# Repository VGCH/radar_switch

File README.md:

# IoT Модуль управления освещением с радарным датчиком

Работает как самостоятельное утройство, так и в составе умного дома Home Assistant:

В модуле реализованы следующие сервисы

> mDNS

> SSDP/UPnP

> Captive Portal

> MQTT Discovery

## Конфигурация устройства в Home Assistant:

## Веб-интерфейс:

Репозиторий содержит исходники:

> Прошивки устройства

> Печатной платы

> Модели корпуса

## В веб-интерфейсе добавлен график для отображения дистанции в реальном времени:

Полное описание в статье на Хабр

[Ссылка на статью ](https://habr.com/ru/articles/979262/)

[Поддержать донатом ](https://dalink.to/cyberex_tech)

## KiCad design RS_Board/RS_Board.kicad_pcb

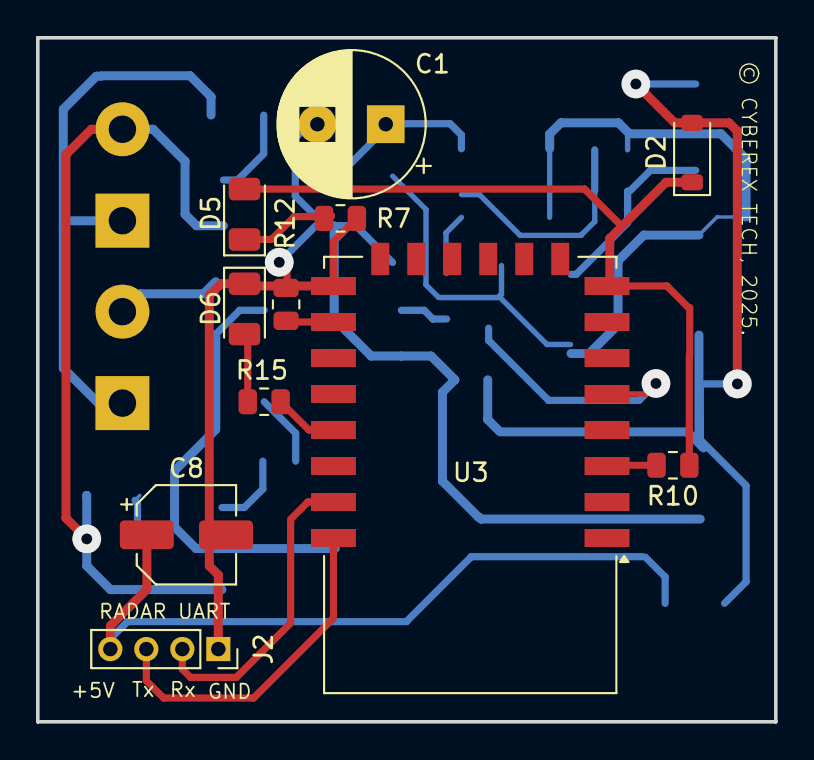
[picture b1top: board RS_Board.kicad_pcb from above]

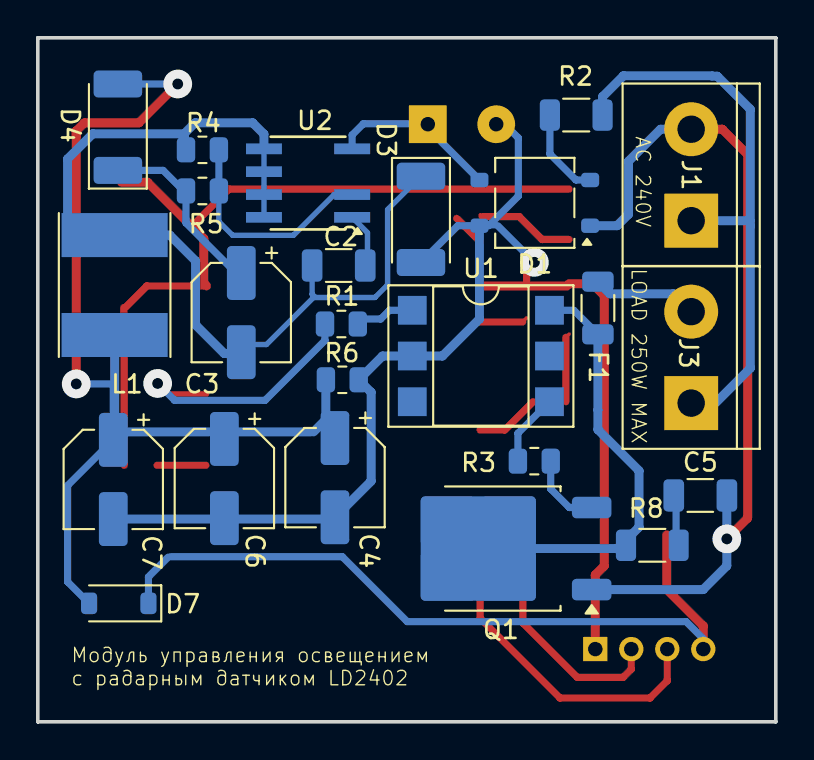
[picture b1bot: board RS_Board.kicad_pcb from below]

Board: 2 copper layers, 41.0 x 38.0 mm, 35 parts (24 on the bottom side), 26 nets.

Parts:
C1: 4.3uF 400V; CP_Radial_D8.0mm_P3.80mm
C2: 100n; C_1206_3216Metric
C3: 45uF 135V; CP_Elec_5x5.4
C4, C6, C7: 220uF 10V; CP_Elec_5x5.4
C5: 10n; C_1206_3216Metric
C8: 220uF 6.3V; CP_Elec_5x5.4
D1: RMB4S; TO-269AA
D2, D7: RB051L-40TE25; D_SOD-123
D3, D4: UF4005 US1J; D_MELF
D5, D6: LED; LED_1206_3216Metric
F1: 1А; R_1206_3216Metric
J1: 240V AC; TerminalBlock_bornier-2_P5.08mm
J2: LD 2402; PinSocket_1x04_P2.00mm_Vertical
J3: LOAD 250W MAX; TerminalBlock_bornier-2_P5.08mm
L1: 1mH; L_Taiyo-Yuden_NR-60xx_HandSoldering
Q1: BT136-600; TO-252-2
R1: 330; R_0805_2012Metric
R2: 0.5; R_1206_3216Metric
R3: 600; R_0805_2012Metric
R4: 1.7k; R_0805_2012Metric
R5: 2.7k; R_0805_2012Metric
R6: 1.5k; R_0805_2012Metric
R7, R10, R12: 1k; R_0805_2012Metric
R8: 39; R_1206_3216Metric
R15: 470; R_0805_2012Metric
U1: MOC3052M; DIP-6_W7.62mm_SMDSocket_SmallPads
U2: LNK362D; PowerIntegrations_SO-8C
U3: ESP-12F; ESP-12E

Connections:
unnamed: C5.1, R8.2
unnamed: C1.1, D1.3 (+), U2.4 (D)
unnamed: C1.2, C4.2, C6.2, C7.2, C8.2, D1.4 (-), D3.2 (A), D6.1 (K), J2.1, R6.2, R7.2, R12.2, U1.2, U3.15 (GND)
unnamed: D1.2, R2.2
unnamed: C4.1, C6.1, C7.1, D2.2 (A), D4.2 (A), D7.2 (A), L1.2, R6.1
unnamed: D2.1 (K), D5.2 (A), R10.2, U3.8 (VCC)
unnamed: C2.1, C3.2, D3.1 (K), L1.1, R4.2, U2.5 (S), U2.6 (S), U2.7 (S), U2.8 (S)
unnamed: C3.1, D4.1 (K), R5.2
unnamed: D5.1 (K), R7.1
unnamed: D6.2 (A), R15.2
unnamed: C8.1, D7.1 (K), J2.4
unnamed: J1.1, J3.1, R2.1
unnamed: C5.2, D1.1, J1.2, Q1.1 (A1)
unnamed: J2.2, U3.21 (GPIO3/RXD)
unnamed: J2.3, U3.22 (GPIO1/TXD)
unnamed: F1.2, J3.2
unnamed: F1.1, Q1.2 (A2), R8.1, U1.6
unnamed: Q1.3 (G), R3.2
unnamed: R1.1, U1.1
unnamed: R3.1, U1.4
unnamed: C2.2, U2.1 (BP)
unnamed: R4.1, R5.1, U2.2 (FB)
unnamed: R10.1, U3.3 (EN)
unnamed: R15.1, U3.19 (GPIO4)
unnamed: R1.2, U3.5 (GPIO14)
unnamed: R12.1, U3.16 (GPIO15)

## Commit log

2025-12-24 Update firmware

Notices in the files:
RS_Board/RS_Board.kicad_pcb:
© CYBEREX TECH, 2025.
